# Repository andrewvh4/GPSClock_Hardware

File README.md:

# GPSClock_Hardware
A modular design for a GPS clock featuring a processor board to recieve and parse GPS data, and a display board to output the time.

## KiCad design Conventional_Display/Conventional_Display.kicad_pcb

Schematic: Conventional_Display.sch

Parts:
C1, C2, C3, C4: 10uF; C_0603_HandSoldering
J1: Conn_01x05; Clock_Board
R1, R2, R3, R4, R5, R6, R7, R8, R9, R10, R11, R12, R13, R14, R15, R16, R17, R18, R19, R20, R21, R22, R23, R24, R25, R26, R27, R28, R29, R30, R31, R32, R33, R34, R35, R36, R37, R38, R39, R40, R41, R42, R43, R44, R45, R46, R47, R48, R49, R50, R51, R52, R53, R54, R55, R56, R57, R58, R59, R60, R61: 500; R_0603_HandSoldering
R62, R63, R64, R65: 10K; R_0603_HandSoldering
U1, U2, U3, U4, U5, U6, U7, U8, U9, U10, U11, U12, U13, U14, U15: 7-Segment_Display_CA; LSH-A101
U16, U17, U18, U19: MAX_7219; SOIC-24W_7.5x15.4mm_Pitch1.27mm
U20, U21, U22, U23: 1088A5_8x8_LED_Matrix; 1088A5_8x8matrix

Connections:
+5V: C1.1, C2.1, C3.1, C4.1, J1.VCC, R62.1, R63.1, R64.1, R65.1, U1.1, U1.6, U2.1, U2.6, U3.1, U3.6, U4.1, U4.6, U5.1, U5.6, U6.1, U6.6, U7.1, U7.6, U8.1, U8.6, U9.1, U9.6, U10.1, U10.6, U11.1, U11.6, U12.1, U12.6, U13.1, U13.6, U14.1, U14.6, U15.1, U15.6, U16.19 (V+), U17.19 (V+), U18.19 (V+), U19.19 (V+)
Clk: J1.CLK, U16.13 (CLK), U17.13 (CLK), U18.13 (CLK), U19.13 (CLK)
Din: J1.DIN, U16.1 (Din)
GND: C1.2, C2.2, C3.2, C4.2, J1.GND, R1.2, R2.2, R3.2, R4.2, R5.2, R6.2, R7.2, R8.2, R9.2, R10.2, R11.2, R12.2, R13.2, R14.2, R15.2, R16.2, R17.2, R18.2, R19.2, R20.2, R21.2, R22.2, R23.2, R24.2, R25.2, R26.2, R27.2, R28.2, R29.2, R30.2, R31.2, R32.2, R33.2, R34.2, R35.2, R36.2, R37.2, R38.2, R39.2, R40.2, R41.2, R42.2, R43.2, R44.2, R45.2, R46.2, R47.2, R48.2, R49.2, R50.2, R51.2, R52.2, R53.2, R54.2, R55.2, R56.2, R57.2, R58.2, R59.2, R60.2, R61.2, U16.4 (GND), U16.9 (GND), U17.4 (GND), U17.9 (GND), U18.4 (GND), U18.9 (GND), U19.4 (GND), U19.9 (GND)
Load: J1.CS, U16.12 (Load), U17.12 (Load), U18.12 (Load), U19.12 (Load)
unnamed: R1.1, U1.9
unnamed: R2.1, U1.8
unnamed: R3.1, U2.10
unnamed: R4.1, U2.9
unnamed: R5.1, U2.5
unnamed: R6.1, U2.4
unnamed: R7.1, U2.3
unnamed: R8.1, U3.10
unnamed: R9.1, U3.9
unnamed: R10.1, U3.8
unnamed: R11.1, U3.5
unnamed: R12.1, U3.3
unnamed: R13.1, U4.9
unnamed: R14.1, U4.8
unnamed: R15.1, U4.2
unnamed: R16.1, U4.3
unnamed: R17.1, U5.10
unnamed: R18.1, U5.8
unnamed: R19.1, U5.5
unnamed: R20.1, U5.2
unnamed: R21.1, U5.3
unnamed: R22.1, U6.10
unnamed: R23.1, U6.8
unnamed: R24.1, U6.5
unnamed: R25.1, U6.4
unnamed: R26.1, U6.2
unnamed: R27.1, U6.3
unnamed: R28.1, U7.10
unnamed: R29.1, U7.9
unnamed: R30.1, U7.8
unnamed: R31.1, U8.10
unnamed: R32.1, U8.9
unnamed: R33.1, U8.8
unnamed: R34.1, U8.5
unnamed: R35.1, U8.4
unnamed: R36.1, U8.2
unnamed: R37.1, U8.3
unnamed: R38.1, U9.10
unnamed: R39.1, U9.9
unnamed: R40.1, U9.8
unnamed: R41.1, U9.2
unnamed: R42.1, U9.3
unnamed: R43.1, U10.9
unnamed: R44.1, U10.8
unnamed: R45.1, U11.9
unnamed: R46.1, U11.8
unnamed: R47.1, U12.9
unnamed: R48.1, U12.8
unnamed: R49.1, U13.10
unnamed: R50.1, U13.9
unnamed: R51.1, U13.8
unnamed: R52.1, U13.5
unnamed: R53.1, U13.4
unnamed: R54.1, U13.2
unnamed: R55.1, U14.9
unnamed: R56.1, U14.8
unnamed: R57.1, U15.10
unnamed: R58.1, U15.9
unnamed: R59.1, U15.5
unnamed: R60.1, U15.4
unnamed: R61.1, U15.3
unnamed: R62.2, U16.18 (ISet)
unnamed: R63.2, U17.18 (ISet)
unnamed: R64.2, U18.18 (ISet)
unnamed: R65.2, U19.18 (ISet)
unnamed: U16.2 (Dig_0), U20.1 (Row_0)
unnamed: U16.3 (Dig_4), U20.9 (Row_4)
unnamed: U16.5 (Dig_6), U20.10 (Row_6)
unnamed: U16.6 (Dig_2), U20.16 (Row_2)
unnamed: U16.7 (Dig_3), U20.4 (Row_3)
unnamed: U16.8 (Dig_7), U20.13 (Row_7)
unnamed: U16.10 (Dig_5), U20.15 (Row_5)
unnamed: U16.11 (Dig_1), U20.6 (Row_1)
unnamed: U16.14 (Seg_A), U20.11 (Col_1)
unnamed: U16.15 (Seg_F), U20.7 (Col_6)
unnamed: U16.16 (Seg_B), U20.12 (Col_2)
unnamed: U16.17 (Seg_G), U20.8 (Col_7)
unnamed: U16.20 (Seg_C), U20.2 (Col_3)
unnamed: U16.21 (Seg_E), U20.3 (Col_5)
unnamed: U16.22 (Seg_DP), U20.5 (Col_0)
unnamed: U16.23 (Seg_D), U20.14 (Col_4)
unnamed: U16.24 (Dout), U17.1 (Din)
unnamed: U17.2 (Dig_0), U21.1 (Row_0)
unnamed: U17.3 (Dig_4), U21.9 (Row_4)
unnamed: U17.5 (Dig_6), U21.10 (Row_6)
unnamed: U17.6 (Dig_2), U21.16 (Row_2)
unnamed: U17.7 (Dig_3), U21.4 (Row_3)
unnamed: U17.8 (Dig_7), U21.13 (Row_7)
unnamed: U17.10 (Dig_5), U21.15 (Row_5)
unnamed: U17.11 (Dig_1), U21.6 (Row_1)
unnamed: U17.14 (Seg_A), U21.11 (Col_1)
unnamed: U17.15 (Seg_F), U21.7 (Col_6)
unnamed: U17.16 (Seg_B), U21.12 (Col_2)
unnamed: U17.17 (Seg_G), U21.8 (Col_7)
unnamed: U17.20 (Seg_C), U21.2 (Col_3)
unnamed: U17.21 (Seg_E), U21.3 (Col_5)
unnamed: U17.22 (Seg_DP), U21.5 (Col_0)
unnamed: U17.23 (Seg_D), U21.14 (Col_4)
unnamed: U17.24 (Dout), U18.1 (Din)
unnamed: U18.2 (Dig_0), U22.1 (Row_0)
unnamed: U18.3 (Dig_4), U22.9 (Row_4)
unnamed: U18.5 (Dig_6), U22.10 (Row_6)
unnamed: U18.6 (Dig_2), U22.16 (Row_2)
unnamed: U18.7 (Dig_3), U22.4 (Row_3)
unnamed: U18.8 (Dig_7), U22.13 (Row_7)
unnamed: U18.10 (Dig_5), U22.15 (Row_5)
unnamed: U18.11 (Dig_1), U22.6 (Row_1)
unnamed: U18.14 (Seg_A), U22.11 (Col_1)
unnamed: U18.15 (Seg_F), U22.7 (Col_6)
unnamed: U18.16 (Seg_B), U22.12 (Col_2)
unnamed: U18.17 (Seg_G), U22.8 (Col_7)
unnamed: U18.20 (Seg_C), U22.2 (Col_3)
unnamed: U18.21 (Seg_E), U22.3 (Col_5)
unnamed: U18.22 (Seg_DP), U22.5 (Col_0)
unnamed: U18.23 (Seg_D), U22.14 (Col_4)
unnamed: U18.24 (Dout), U19.1 (Din)
unnamed: U19.2 (Dig_0), U23.1 (Row_0)
unnamed: U19.3 (Dig_4), U23.9 (Row_4)
unnamed: U19.5 (Dig_6), U23.10 (Row_6)
unnamed: U19.6 (Dig_2), U23.16 (Row_2)
unnamed: U19.7 (Dig_3), U23.4 (Row_3)
unnamed: U19.8 (Dig_7), U23.13 (Row_7)
unnamed: U19.10 (Dig_5), U23.15 (Row_5)
unnamed: U19.11 (Dig_1), U23.6 (Row_1)
unnamed: U19.14 (Seg_A), U23.11 (Col_1)
unnamed: U19.15 (Seg_F), U23.7 (Col_6)
unnamed: U19.16 (Seg_B), U23.12 (Col_2)
unnamed: U19.17 (Seg_G), U23.8 (Col_7)
unnamed: U19.20 (Seg_C), U23.2 (Col_3)
unnamed: U19.21 (Seg_E), U23.3 (Col_5)
unnamed: U19.22 (Seg_DP), U23.5 (Col_0)
unnamed: U19.23 (Seg_D), U23.14 (Col_4)

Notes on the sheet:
Quadrant 1
Quadrant 2
Quadrant 3
Quadrant 4
Digits
Conn

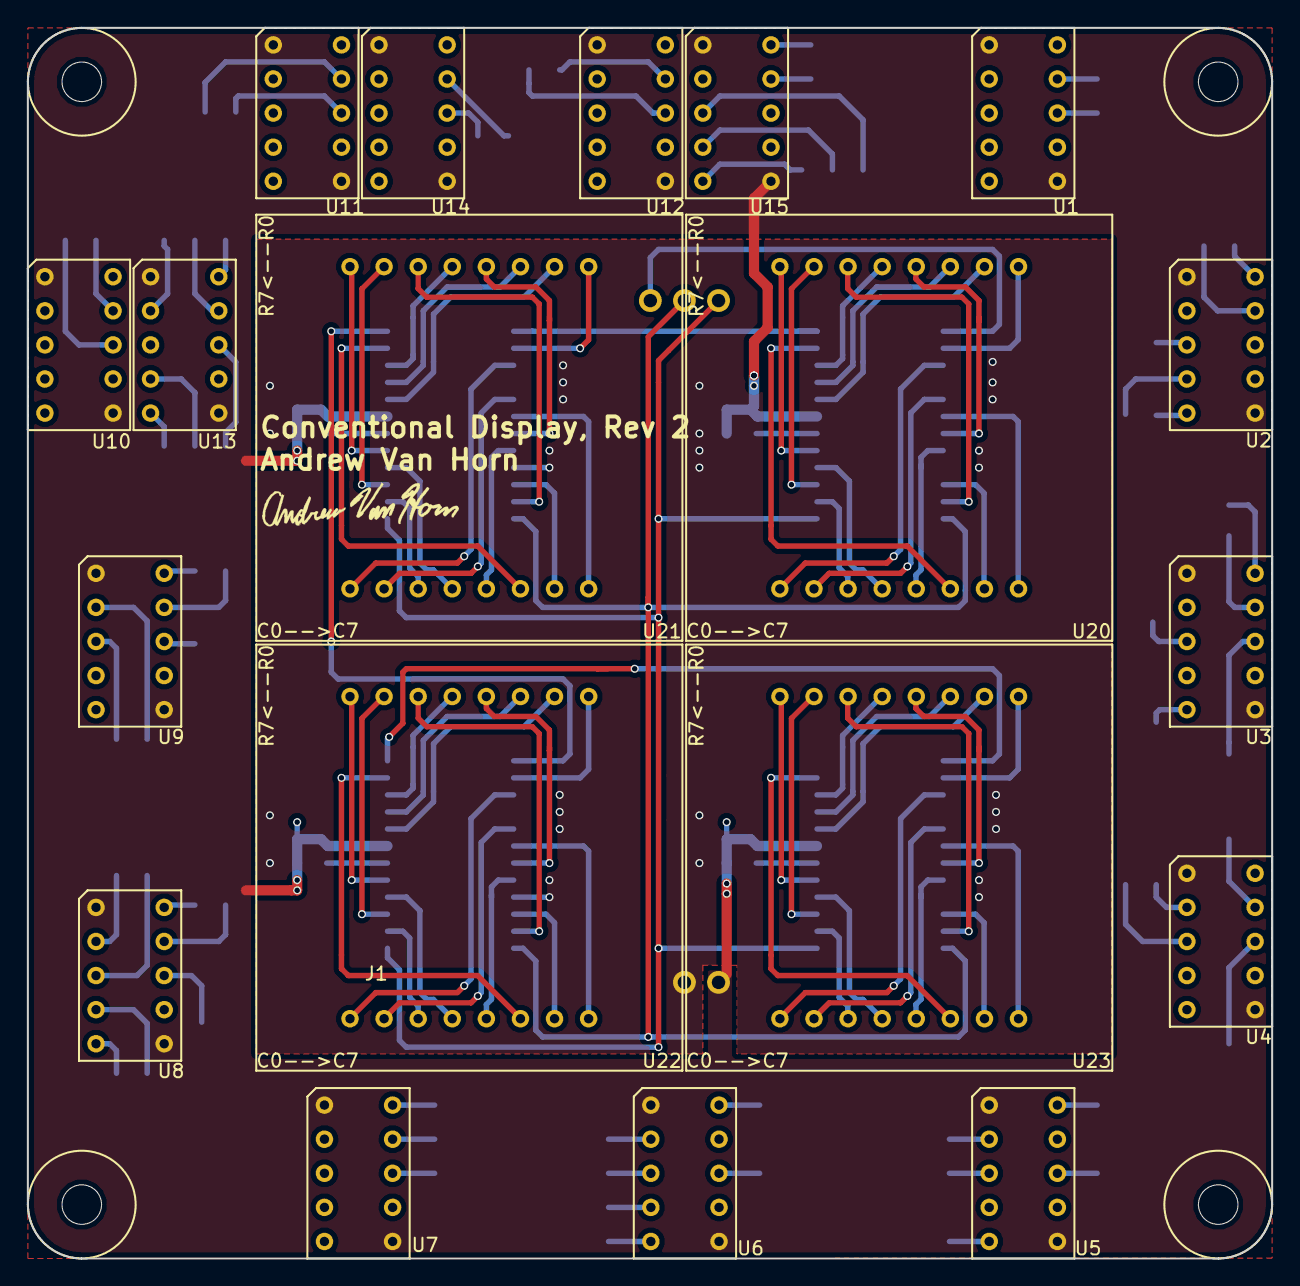
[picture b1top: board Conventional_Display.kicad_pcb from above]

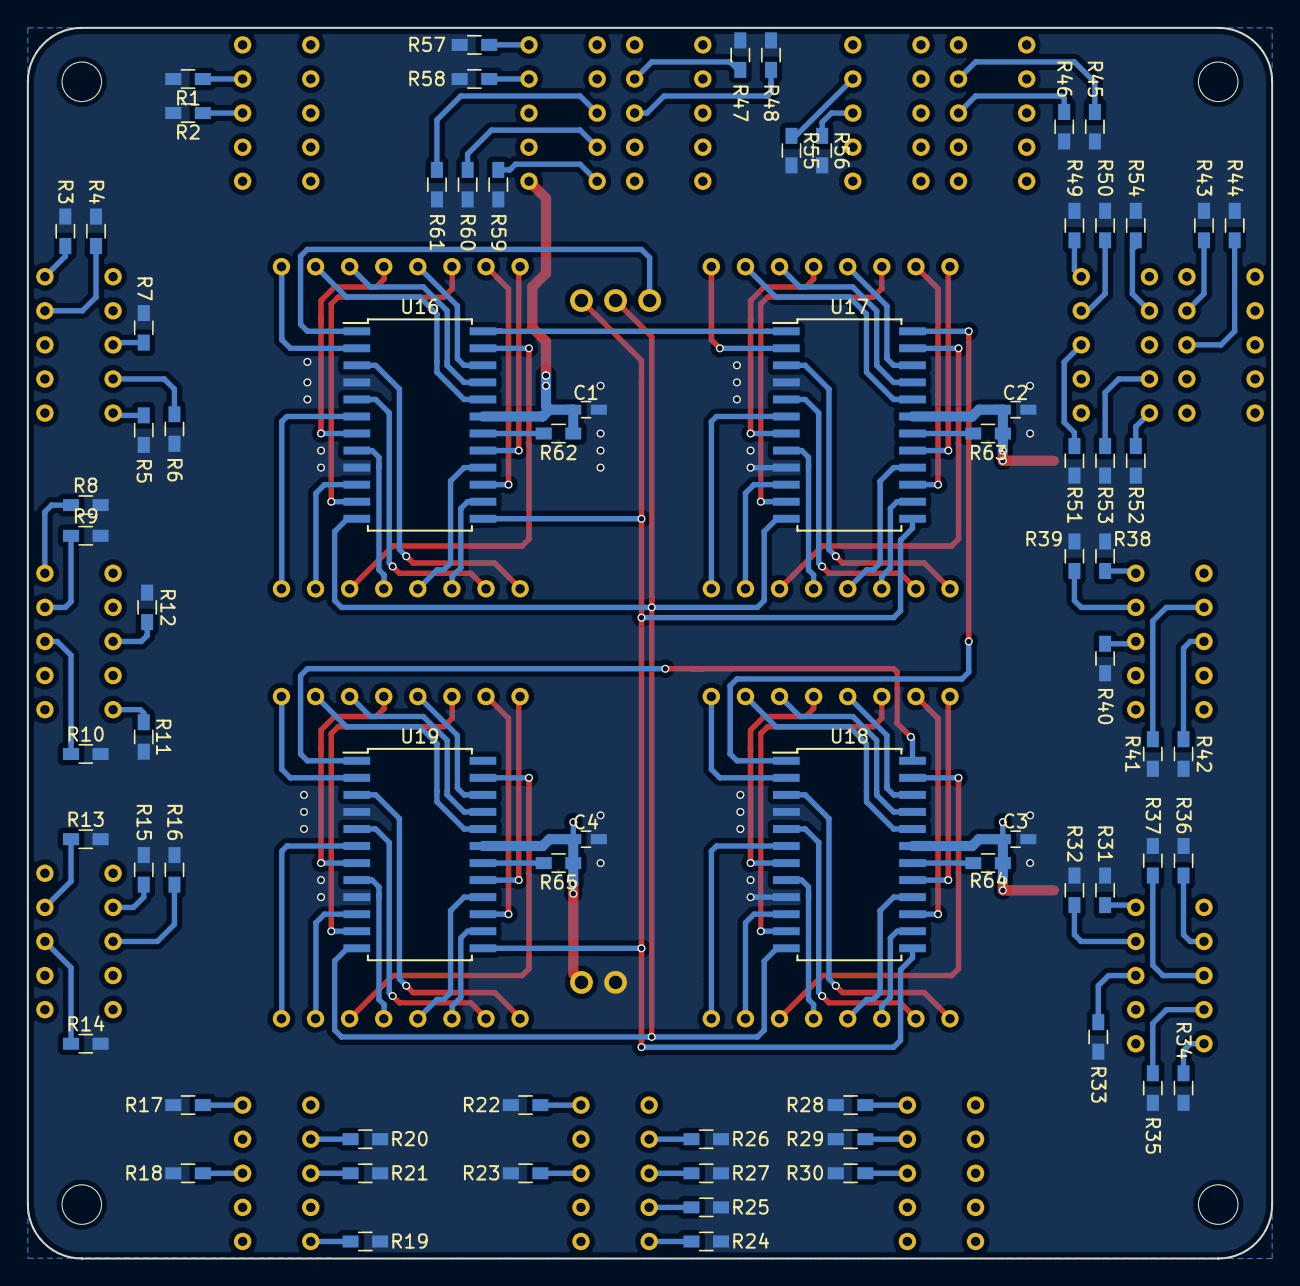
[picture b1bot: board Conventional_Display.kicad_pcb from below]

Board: 2 copper layers, 92.7 x 91.7 mm, 93 parts (73 on the bottom side), 137 nets.

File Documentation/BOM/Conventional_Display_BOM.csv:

Id,Designator,Package,Designation,,Item Name,Part Number,,,Vendor,Quantity,Cost Per Item,,Cost,,Comments,URL
1,"U21,U23,U20,U22",1088A5_8x8matrix,1088A5_8x8_LED_Matrix,,HiLetgo MAX7219 Dot Matrix,B07FFV537V,,,Amazon,4,,,8.49,,You can also desolder the MAX7219 from here,https://www.amazon.com/gp/product/B07FFV537V/ref=ppx_yo_dt_b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
3,"R63,R62,R64,R65",R_0603_HandSoldering,10K,,0603 Resistor 10K,RHM10KADCT-ND,,,Digikey,8,0.1,,0.8,,,https://www.digikey.com/product-detail/en/rohm-semiconductor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
4,"U8,U4,U1,U2,U3,U5,U6,U7,U9,U10,U11,U12,U13,U14,U15",LSHD-A101,7-Segment_Display_CA,,"DISPLAY 7-SEG 0.3"" SGL RED 10DIP",160-1572-5-ND,,,Digikey,15,1.056,,15.84,,,https://www.digikey.com/product-detail/en/lite-on-inc/LSHD-A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
5,"U16,U17,U18,U19",SOIC-24W_7.5x15.4mm_Pitch1.27mm,MAX_7219,,MAX7219CWG+T,MAX7219CWG+TCT-ND,,,Digikey,4,8.95,,8.95,,Can desolder from: https://www.amazon.com/gp/product/B07FFV537V/ref=ppx_yo_dt_b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,https://www.digikey.com/product-detail/en/maxim-integrated/M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
6,"C1,C2,C3,C4",C_0603_HandSoldering,10uF,,10uF 0603 Capacitor,490-10728-1-ND,,,Digikey,4,0.32,,0.64,,,https://www.digikey.com/product-detail/en/murata-electronics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
7,"R1,R2,R3,R4,R5,R6,R7,R8,R9,R10,R11,R12,R13,R14,R15,R16,R17,R18,R19,R20,R21,R22,R23,R24,R25,R26,R27,R28,R29,R30,R31,R32,R33,R34,R35,R36,R37,R38,R39,R40,R41,R42,R43,R44,R45,R46,R47,R48,R49,R50,R51,R52,R53,R54,R55,R56,R57,R58,R59,R60,R61",R_0603_HandSoldering,500,,0603 Resistor 500,RHM510DCT-ND,,,Digikey,61,0.1,,0.7,,,https://www.digikey.com/product-detail/en/rohm-semiconductor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
8,J1,Clock_Board,Conn_01x02,,CONN HDR 2POS 0.1 GOLD PCB,S7035-ND,,,Digikey,1,0.33,,0.33,,,https://www.digikey.com/product-detail/en/sullins-connector-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
9,J1,Clock_Board,Conn_01x03,,CONN HDR 3POS 0.1 GOLD PCB,S7036-ND,,,Digikey,1,0.37,,0.37,,,https://www.digikey.com/product-detail/en/sullins-connector-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

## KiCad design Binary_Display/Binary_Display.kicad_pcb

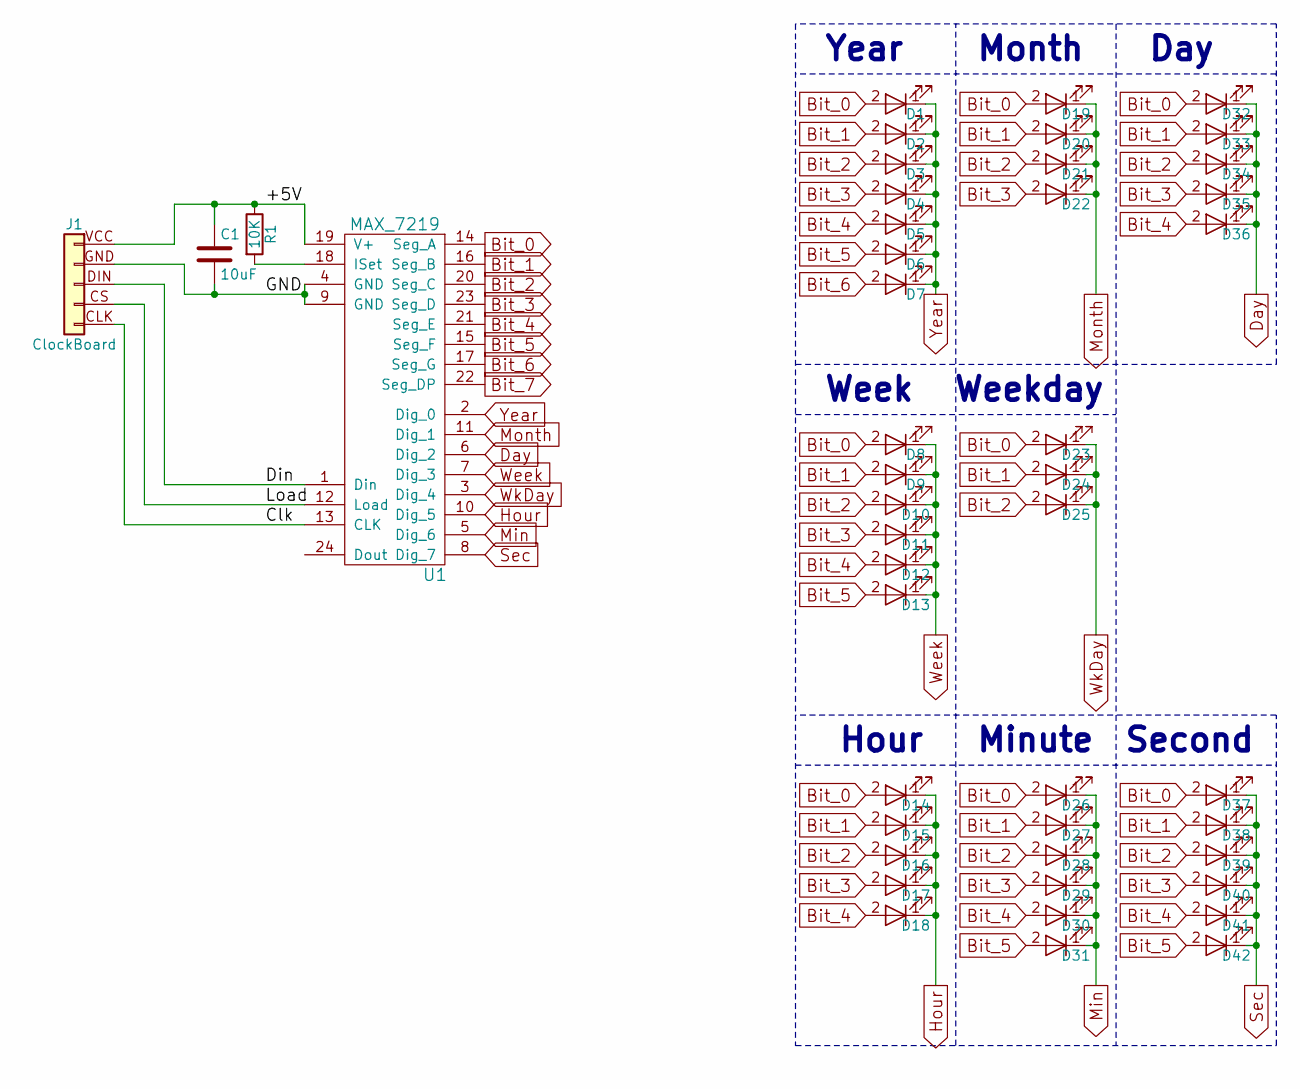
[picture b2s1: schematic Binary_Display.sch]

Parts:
C1: 10uF; C_0603_HandSoldering
D1, D2, D3, D4, D5, D6, D7, D8, D9, D10, D11, D12, D13, D14, D15, D16, D17, D18, D19, D20, D21, D22, D23, D24, D25, D26, D27, D28, D29, D30, D31, D32, D33, D34, D35, D36, D37, D38, D39, D40, D41, D42: LED; LED_D5.0mm
J1: ClockBoard; Clock_Board
R1: 10K; R_0603_HandSoldering
U1: MAX_7219; SOIC-24W_7.5x15.4mm_Pitch1.27mm

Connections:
/+5V: C1.1, J1.VCC (Pin_1), R1.1, U1.19 (V+)
/Clk: J1.CLK (Pin_5), U1.13 (CLK)
/Din: J1.DIN (Pin_3), U1.1 (Din)
/GND: C1.2, J1.GND (Pin_2), U1.4 (GND), U1.9 (GND)
/Load: J1.CS (Pin_4), U1.12 (Load)
Bit_0: D1.2 (A), D8.2 (A), D14.2 (A), D19.2 (A), D23.2 (A), D26.2 (A), D32.2 (A), D37.2 (A), U1.14 (Seg_A)
Bit_1: D2.2 (A), D9.2 (A), D15.2 (A), D20.2 (A), D24.2 (A), D27.2 (A), D33.2 (A), D38.2 (A), U1.16 (Seg_B)
Bit_2: D3.2 (A), D10.2 (A), D16.2 (A), D21.2 (A), D25.2 (A), D28.2 (A), D34.2 (A), D39.2 (A), U1.20 (Seg_C)
Bit_3: D4.2 (A), D11.2 (A), D17.2 (A), D22.2 (A), D29.2 (A), D35.2 (A), D40.2 (A), U1.23 (Seg_D)
Bit_4: D5.2 (A), D12.2 (A), D18.2 (A), D30.2 (A), D36.2 (A), D41.2 (A), U1.21 (Seg_E)
Bit_5: D6.2 (A), D13.2 (A), D31.2 (A), D42.2 (A), U1.15 (Seg_F)
Bit_6: D7.2 (A), U1.17 (Seg_G)
Day: D32.1 (K), D33.1 (K), D34.1 (K), D35.1 (K), D36.1 (K), U1.6 (Dig_2)
Hour: D14.1 (K), D15.1 (K), D16.1 (K), D17.1 (K), D18.1 (K), U1.10 (Dig_5)
Min: D26.1 (K), D27.1 (K), D28.1 (K), D29.1 (K), D30.1 (K), D31.1 (K), U1.5 (Dig_6)
Month: D19.1 (K), D20.1 (K), D21.1 (K), D22.1 (K), U1.11 (Dig_1)
unnamed: R1.2, U1.18 (ISet)
Sec: D37.1 (K), D38.1 (K), D39.1 (K), D40.1 (K), D41.1 (K), D42.1 (K), U1.8 (Dig_7)
Week: D8.1 (K), D9.1 (K), D10.1 (K), D11.1 (K), D12.1 (K), D13.1 (K), U1.7 (Dig_3)
WkDay: D23.1 (K), D24.1 (K), D25.1 (K), U1.3 (Dig_4)
Year: D1.1 (K), D2.1 (K), D3.1 (K), D4.1 (K), D5.1 (K), D6.1 (K), D7.1 (K), U1.2 (Dig_0)

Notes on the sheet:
Year
Month
Day
Week
Weekday
Hour
Minute
Second

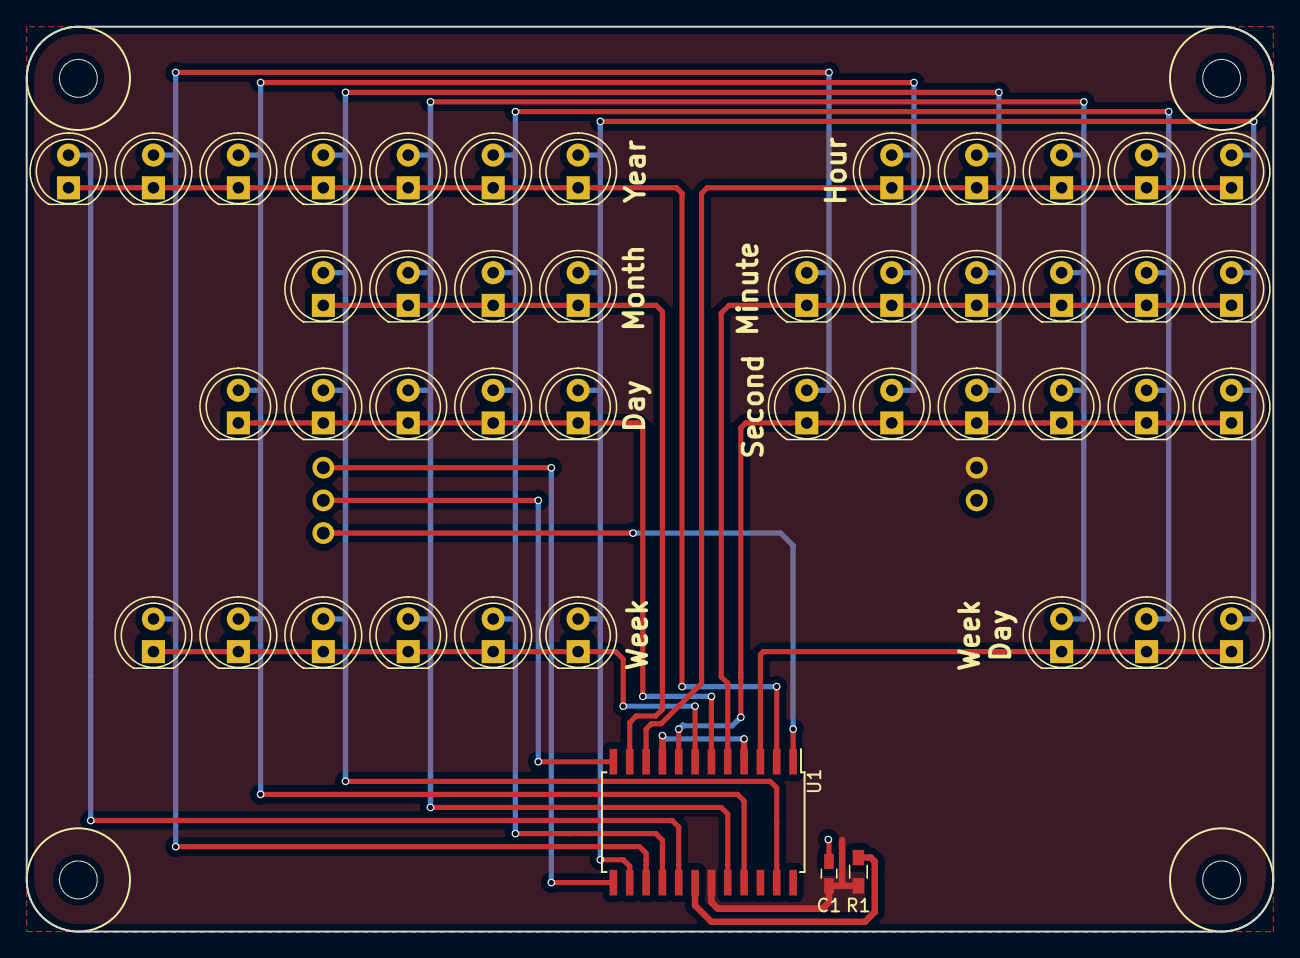
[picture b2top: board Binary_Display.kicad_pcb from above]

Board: 2 copper layers, 96.9 x 70.4 mm, 46 parts (0 on the bottom side), 21 nets.

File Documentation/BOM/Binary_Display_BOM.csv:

Id,Designator,Package,Designation,,Item Name,Part Number,,,Vendor,Quantity,Cost Per Item,,Cost,,Comments,URL
1,U1,SOIC-24W_7.5x15.4mm_Pitch1.27mm,MAX_7219,,MAX7219CWG+T,MAX7219CWG+TCT-ND,,,Digikey,1,8.95,,8.95,,Can desolder from: https://www.amazon.com/gp/product/B07FFV537V/ref=ppx_yo_dt_b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,https://www.digikey.com/product-detail/en/maxim-integrated/M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
2,"D31,D1,D2,D3,D4,D5,D6,D7,D8,D9,D10,D11,D12,D13,D14,D15,D16,D17,D18,D19,D20,D21,D22,D23,D24,D25,D26,D27,D28,D29,D30,D32,D33,D34,D35,D36,D37,D38,D39,D40,D41,D42",LED_D5.0mm,LED,,5mm SMD LED,,,,Amazon,42,,,12.99,,Any 5mm LED will work,https://www.amazon.com/dp/B073QMYKDM/ref=sspa_dk_detail_1?ps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
3,C1,C_0603_HandSoldering,10uF,,10uF 0603 Capacitor,490-10728-1-ND,,,Digikey,1,0.32,,0.64,,,https://www.digikey.com/product-detail/en/murata-electronics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
4,R1,R_0603_HandSoldering,10K,,0603 Resistor 10K,RHM10KADCT-ND,,,Digikey,1,0.1,,0.8,,,https://www.digikey.com/product-detail/en/rohm-semiconductor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
5,J1,Clock_Board,ClockBoard,,,,,,,1,,,,,,

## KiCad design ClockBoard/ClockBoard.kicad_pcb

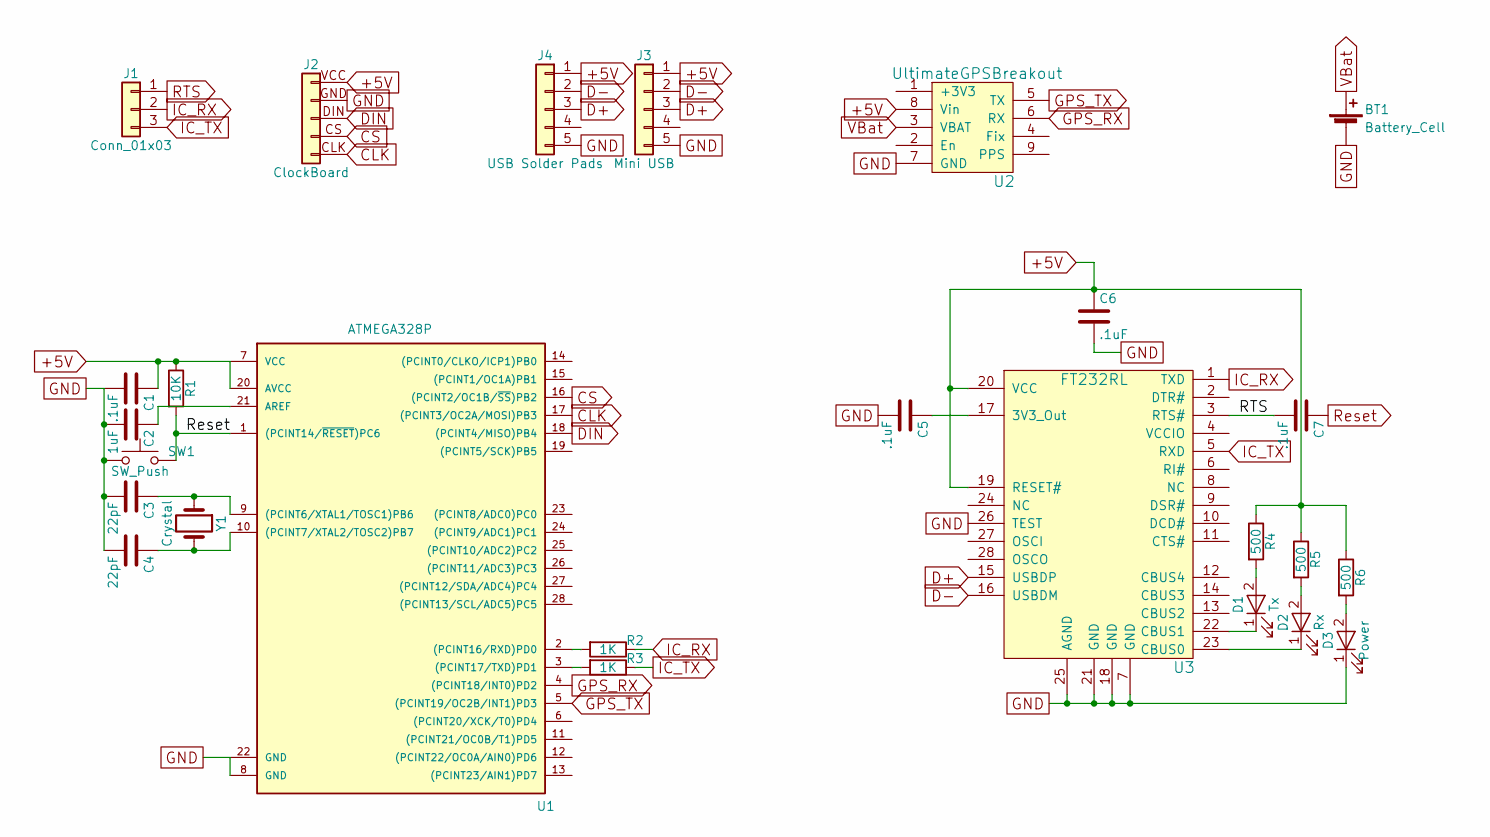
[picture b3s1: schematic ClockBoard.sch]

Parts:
BT1: Battery_Cell; CR1220_Battery_Holder
C1, C5, C6, C7: .1uF; C_0603_HandSoldering
C2: 1uF; C_0603_HandSoldering
C3, C4: 22pF; C_0603_HandSoldering
D1: Tx; D_0603
D2: Rx; D_0603
D3: Power; D_0603
J1: Conn_01x03; Pin_Header_Straight_1x03_Pitch2.54mm
J2: ClockBoard; Clock_Board
J3: Mini USB; MiniUSB_SMT
J4: USB Solder Pads; Pin_Header_Straight_1x05_Pitch2.54mm
R1: 10K; R_0603_HandSoldering
R2, R3: 1K; R_0603_HandSoldering
R4, R5, R6: 500; R_0603_HandSoldering
SW1: SW_Push; SPST_Pushbutton
U1: ATMEGA328P; DIP-28_W7.62mm
U2: UltimateGPSBreakout; Ultimate_GPS_Breakout
U3: FT232RL; SSOP-28_5.3x10.2mm_Pitch0.65mm
Y1: Crystal; Crystal_SMD_HC49-SD_HandSoldering

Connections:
+5V: C1.1, C6.1, J2.VCC (Pin_1), J3.1, J4.1, R1.1, R4.1, R5.1, R6.1, U1.7 (VCC), U1.20 (AVCC), U2.8 (Vin), U3.19 (RESET#), U3.20 (VCC)
CLK: J2.CLK (Pin_5), U1.17 ((PCINT3/OC2A/MOSI)PB3)
CS: J2.CS (Pin_4), U1.16 ((PCINT2/OC1B/~SS~)PB2)
D+: J3.3, J4.3, U3.15 (USBDP)
D-: J3.2, J4.2, U3.16 (USBDM)
DIN: J2.DIN (Pin_3), U1.18 ((PCINT4/MISO)PB4)
GND: BT1.2 (-), C1.2, C2.2, C3.2, C4.2, C5.2, C6.2, D3.1 (K), J2.GND (Pin_2), J3.5, J4.5, SW1.1, U1.8 (GND), U1.22 (GND), U2.7 (GND), U3.7 (GND), U3.18 (GND), U3.21 (GND), U3.25 (AGND), U3.26 (TEST)
GPS_RX: U1.4 ((PCINT18/INT0)PD2), U2.6 (RX)
GPS_TX: U1.5 ((PCINT19/OC2B/INT1)PD3), U2.5 (TX)
IC_RX: J1.2, R2.1, U3.1 (TXD)
IC_TX: J1.3, R3.1, U3.5 (RXD)
unnamed: C2.1, U1.21 (AREF)
unnamed: C3.1, U1.9 ((PCINT6/XTAL1/TOSC1)PB6), Y1.1
unnamed: C4.1, U1.10 ((PCINT7/XTAL2/TOSC2)PB7), Y1.2
unnamed: C5.1, U3.17 (3V3_Out)
unnamed: D1.1 (K), U3.22 (CBUS1)
unnamed: D1.2 (A), R4.2
unnamed: D2.1 (K), U3.23 (CBUS0)
unnamed: D2.2 (A), R5.2
unnamed: D3.2 (A), R6.2
unnamed: R2.2, U1.2 ((PCINT16/RXD)PD0)
unnamed: R3.2, U1.3 ((PCINT17/TXD)PD1)
RTS: C7.2, J1.1, U3.3 (RTS#)
Reset: C7.1, R1.2, SW1.2, U1.1 ((PCINT14/~RESET~)PC6)
VBat: BT1.1 (+), U2.3 (VBAT)

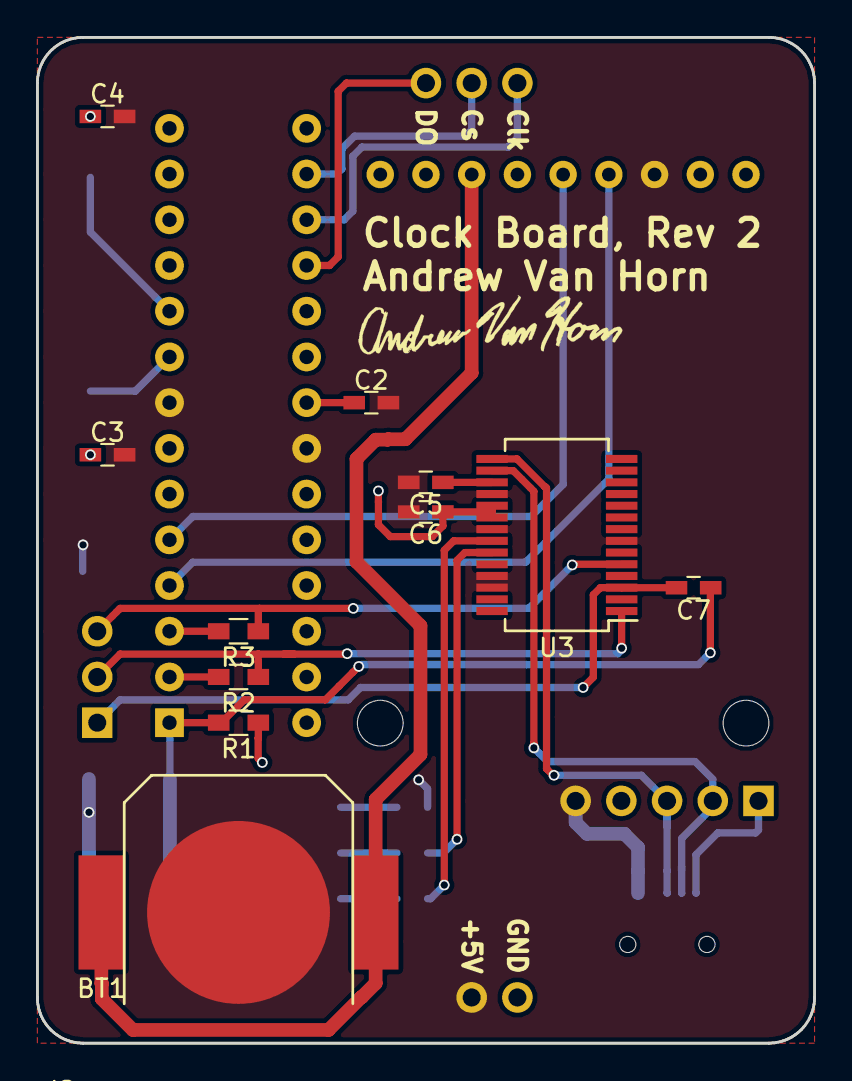
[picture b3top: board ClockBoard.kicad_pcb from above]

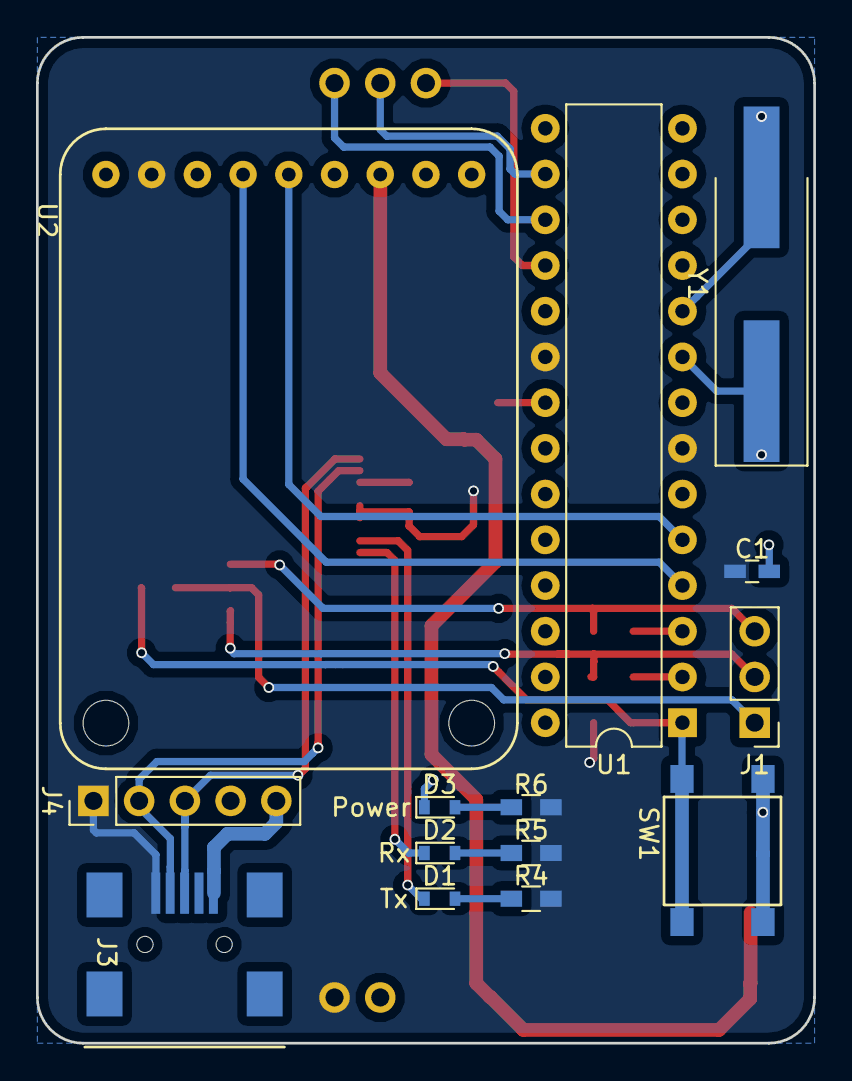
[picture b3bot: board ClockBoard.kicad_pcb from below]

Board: 2 copper layers, 43.2 x 55.9 mm, 26 parts (14 on the bottom side), 25 nets.

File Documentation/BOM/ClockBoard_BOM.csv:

Id,Designator,Package,Designation,,Item Name,Part Number,,,Vendor,Quantity,Cost Per Item,,Cost,,Comments,URL
1,U2,Ultimate_GPS_Breakout,UltimateGPSBreakout,,GPS BREAKOUT 66CH W/10HZ UPDATES,1528-1153-ND,,,Digikey,1,39.95,,39.95,,,https://www.digikey.com/products/en?mpart=746&v=1528
2,"C1,C5,C6,C7",C_0603_HandSoldering,.1uF,,.1uF 0603 Capacitor,399-1100-1-ND,,,Digikey,4,0.1,,0.4,,,https://www.digikey.com/product-detail/en/kemet/C0603C104Z3V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
3,C2,C_0603_HandSoldering,1uF,,1uF 0603 Capacitor,1276-1182-1-ND,,,Digikey,1,0.1,,0.1,,,https://www.digikey.com/product-detail/en/samsung-electro-me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
4,"C3,C4",C_0603_HandSoldering,22pF,,22pF 0603 Capacitor,399-7874-1-ND,,,Digikey,2,0.1,,0.2,,,https://www.digikey.com/product-detail/en/kemet/C0603C220J1G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
5,D1,D_0603,Tx,,LED 0603 Yellow,350-2032-1-ND,,,Digikey,2,0.51,,1.02,,,https://www.digikey.com/product-detail/en/dialight/598804010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
6,D2,D_0603,Rx,,LED 0603 Yellow,350-2032-1-ND,,,Digikey,2,0.51,,1.02,,,https://www.digikey.com/product-detail/en/dialight/598804010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
7,D3,D_0603,Power,,LED 0603 Green,160-1443-1-ND,,,Digikey,8,0.23,,1.84,,,https://www.digikey.com/product-detail/en/lite-on-inc/LTST-C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
8,R1,R_0603_HandSoldering,10K,,0603 Resistor 10K,RHM10KADCT-ND,,,Digikey,1,0.1,,0.1,,,https://www.digikey.com/product-detail/en/rohm-semiconductor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
9,"R2,R3",R_0603_HandSoldering,1K,,0603 Resistor 10K,RHM10KADCT-ND,,,Digikey,2,0.1,,0.2,,,https://www.digikey.com/product-detail/en/rohm-semiconductor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
10,"R4,R5,R6",R_0603_HandSoldering,500,,0603 Resistor 500,RHM510DCT-ND,,,Digikey,3,0.1,,0.3,,,https://www.digikey.com/product-detail/en/rohm-semiconductor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
11,SW1,SPST_Pushbutton,SW_Push,,Pushbutton Switch,CKN9088CT-ND,,,Digikey,1,0.22,,0.22,,,https://www.digikey.com/products/en?keywords=CKN9088CT-ND
12,U3,SSOP-28_5.3x10.2mm_Pitch0.65mm,FT232RL,,FTDI,FT232RL,,,Digikey,1,4.5,,4.5,,,https://www.digikey.com/product-detail/en/ftdi-future-techno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
13,Y1,Crystal_SMD_HC49-SD_HandSoldering,Crystal,,8MHz Crystal,XC1592CT-ND,,,Digikey,1,1.71,,1.71,,,https://www.digikey.com/products/en?keywords=XC1592CT-ND
14,J3,MiniUSB_SMT,Mini USB,,SMD Mini USB,151-1206-1-ND,,,Digikey,1,0.54,,0.54,,,https://www.digikey.com/product-detail/en/edac-inc/690-005-2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
15,BT1,CR1220_Battery_Holder,Battery_Cell,,BATTERY RETAINER COIN 12MM SMD,36-3000-ND,,,Digikey,1,0.52,,0.52,,,https://www.digikey.com/product-detail/en/keystone-electroni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
16,U1,DIP-28_W7.62mm,ATMEGA328P,,ATMEGA328PU,ATMEGA328-PU-ND,,,Digikey,1,1.96,,1.96,,,https://www.digikey.com/product-detail/en/microchip-technolo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
17,U1,DIP-28_W7.62mm,ATMEGA328P,,ATMEGA 328 Housing,ED3050-5-ND,,,Digikey,1,0.33,,0.33,,,https://www.digikey.com/products/en?keywords=ED3050-5-ND

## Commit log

2018-07-11 Board Design for Binary and Conventional Display
2018-08-15 Created clock board
2018-08-18 Made Clock Board
2018-08-29 Removed Had Display
2018-08-29 Removed Unnecesary Files
2018-08-29 Added ToDo
2018-10-05 generated Gerbs
2020-06-01 Created BOM for all boards
2020-06-01 Added silkscreen to boards and organized gerbs
2020-06-09 re routed conventional display LED matrix traces.
